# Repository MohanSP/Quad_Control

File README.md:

# Quad_Control
Control algorithm for an indoor quadcopter

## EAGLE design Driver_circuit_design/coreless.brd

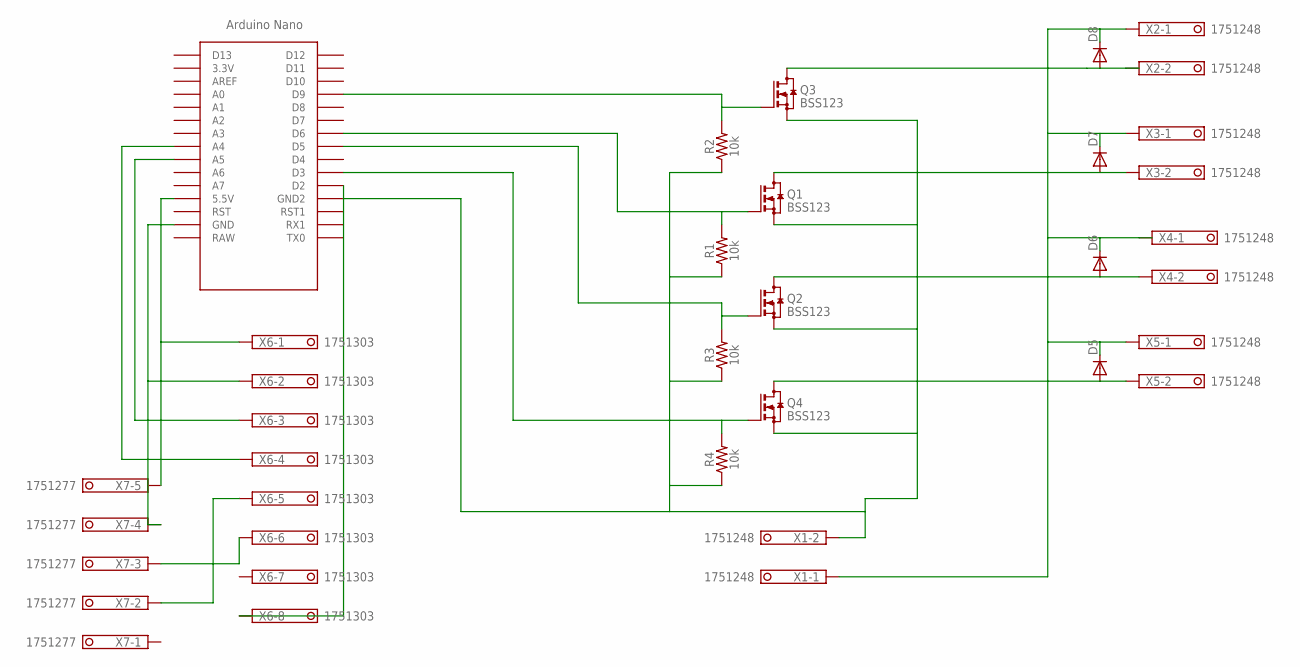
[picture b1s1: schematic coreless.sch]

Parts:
D5, D6, D7, D8: DIODE-DO-214AC; DO-214AC
Q1, Q2, Q3, Q4: BSS123; SOT23
R1, R2, R3, R4: 10k; 0603
U$1: NANO
X1, X2, X3, X4, X5: 1751248
X6: 1751303
X7: 1751277

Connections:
unnamed: Q1.2 (S), Q2.2 (S), Q3.2 (S), Q4.2 (S), R1.1, R2.1, R3.1, R4.1, U$1.GND1 (GND2), X1.2
unnamed: D8.A, Q3.3 (D), X2.2
unnamed: Q3.1 (G), R2.2, U$1.D9
unnamed: D7.A, Q1.3 (D), X3.2
unnamed: Q1.1 (G), R1.2, U$1.D6
unnamed: D6.A, Q2.3 (D), X4.2
unnamed: Q2.1 (G), R3.2, U$1.D5
unnamed: D5.A, Q4.3 (D), X5.2
unnamed: Q4.1 (G), R4.2, U$1.D3
unnamed: U$1.5V (5.5V), X6.1, X7.5
unnamed: U$1.GND, X6.2, X7.4
unnamed: U$1.A5, X6.3
unnamed: U$1.A4, X6.4
unnamed: U$1.D2, X6.8
unnamed: X6.5, X7.2
unnamed: X6.6, X7.3
unnamed: D5.C, D6.C, D7.C, D8.C, X1.1, X2.1, X3.1, X4.1, X5.1

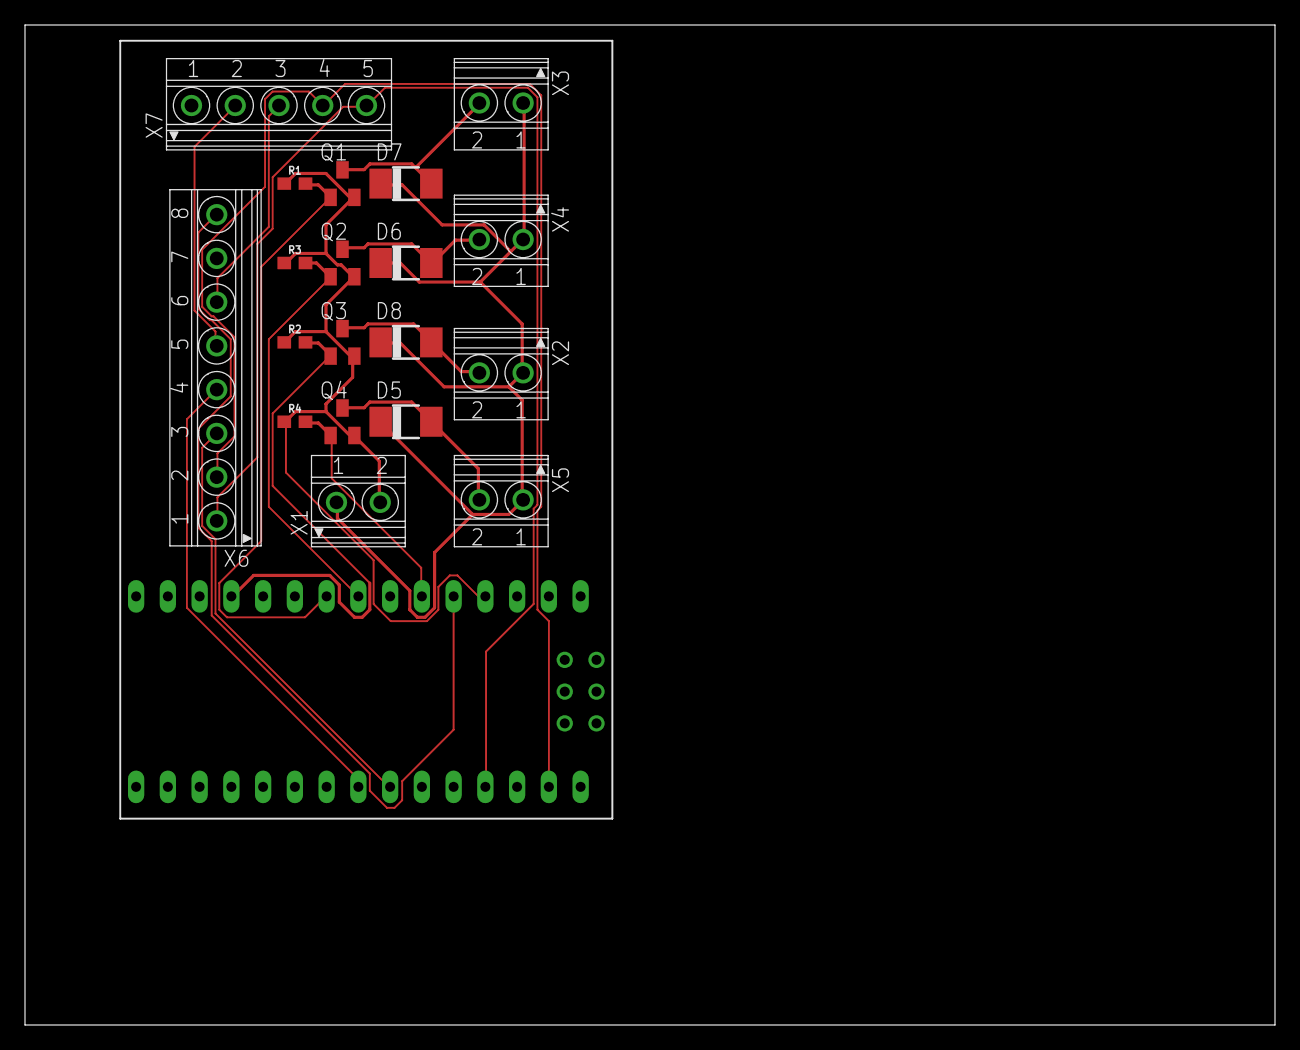
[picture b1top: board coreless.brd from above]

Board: 2 copper layers, 100.0 x 80.0 mm, 20 parts (0 on the bottom side), 17 nets.

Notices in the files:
parts and their libraries:
SparkFun-Resistors: Licensing: Creative Commons ShareAlike 4.0 International - https://creativecommons.org/licenses/by-sa/4.0
